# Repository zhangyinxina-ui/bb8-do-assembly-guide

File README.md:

# BB-8 & D-O 1:1 Assembly Guide

[中文在线装配网站](https://zhangyinxina-ui.github.io/bb8-do-assembly-guide/) · [English build guide](https://zhangyinxina-ui.github.io/bb8-do-assembly-guide/en/) · [权利与再分发边界](NOTICE.md)

一个面向个人制作者的公开工程记录：包含《星球大战：原力觉醒》BB-8 的 1:1 屏幕参考 Blender 模型、三视图、内部运动机构、运动学/动力学验证、控制器草案，以及 D-O 合法公开资源和采购门控路线。

## 当前基准

- BB-8 身体球：Ø508 mm。
- 头部最大直径：Ø295 mm。
- 无天线总高：670 mm，对齐 StarWars.com 公开的 0.67 m。
- Blender 主工程 Stage 19 重开审计：386 个总对象、182 个内部对象，其中 150 个制造对象、9 个非制造工程标记和 23 个 `non_fabrication_reference` 预 CAD 门控对象；主文件 SHA-256 为 `ecd9a8b02db7c0b253c06005aaf16e7a8bf10147f8adec9c8900415e18b38af4`。
- 阶段14质量账本：名义8.463 kg、名义质心z=-56.2 mm、最不利角点z=-27.7 mm；0.6 N·m连续扭矩按2×余量时目标加速度降额为0.70 m/s²。17组质量仍需实物称重。
- 双轮差速内车、310 mm 轮距、6+6 磁体随动头和 40 N 装机拉脱力验收合同。
- 编码器轮速 PI + IMU 偏航闭环仿真：直线 RMS 误差 0.00772 m/s、转角 91.20°，传感器过期同周期撤销 PWM。
- ESP32-S3 已编译双正交编码器与 MPU6050 适配；CPR默认为0、静止标定未完成时保持拒动。
- 双 INA226 电流适配、开漏 ALERT、显式限值、过流/堵转回放与11类锁存故障已编译验证；阶段19将原ALERT→EN假设改为适配MDD20A的ALERT_N→PWM许可级，实体测试仍为 `NOT_RUN`。
- 阶段15新增左右电机驱动包络、双散热器、主保险丝、常开接触器、双通道常闭急停、安全继电器、维护断电与系留急停插口；3°动态坡道解析点为0.289 N·m/电机、2.07×连续扭矩裕量和4.22°合成倾角。器件型号与实体测试仍未冻结。
- 阶段16新增19项强制真机调试门、固定字段ESP32遥测解析器和带文件SHA-256的证据审计；当前结果为 `HOLD_PHYSICAL_TESTS_NOT_RUN`，0/19通过。
- 阶段17用厂商官方资料筛选MDD20A、30 A MIDI保险丝、SW60接触器和P28A 4S2P候选；15/15额定检查通过，但因堵转、再生、独立去能适配、BMS与电池包未冻结，结果保持 `HOLD_COMPONENT_FREEZE_MEASUREMENTS_REQUIRED`。
- 阶段18完成REC Active BMS 4S、MDD20A、SW60、MIDI保险丝、外置分流器与双通道门板的模块化电源舱解析布局，并已写入唯一Blender主工程；重开审计确认363个总对象、159个内部对象、150个制造对象、9个工程标记和39个阶段18对象。8个候选包络满足球壳/候选/既有机构间隙门，但12项实物尺寸与接口仍未冻结，结果保持 `HOLD_PHYSICAL_FIT_AND_INTERFACE_VALIDATION_REQUIRED`。
- 阶段19发布双许可PWM门正式KiCad 10原理图与50 × 35 mm两层布线PCB，并把23个非制造板件/器件参考包络写入唯一Blender主工程；重开审计与新导出已通过。SAFE_A、SAFE_B、双INA226 `ALERT_N`与3.3 V掉电均可独立阻断左右PWM；64/64真值组合、0项ERC违规、0项PCB DRC违规、0个未连接项，以及34个器件引用/91条规范引脚连接/21个网络交叉审计通过。但尚无独立原理图/布局同行复核、Gerber/钻孔发布复核、实装板或台架波形，结果保持 `HOLD_PCB_CAD_BENCH_AND_SAFETY_VALIDATION_REQUIRED`。
- 阶段20发现并封锁旧结构分析漂移：当前制造清单的磁力桅杆是Ø24 × 340 mm，而阶段2仍按Ø12/Ø8 × 300 mm铝管计算。新门以当前数字几何筛查2.5 g垂向/1.0 g侧向载荷、斜撑屈曲、纵梁/横梁挠度、PCD35电机安装需求、理想基材疲劳和桅杆模态；解析检查通过，但轮—壳接触还缺5.5 mm径向调节预算，15项材料/连接/公差/实物门全部未关闭，结果保持 `HOLD_JOINT_TOLERANCE_MATERIAL_AND_PHYSICAL_VALIDATION_REQUIRED`。
- D-O v3.4.3 的 D0/D1 舵机—Serial0 冲突已形成固定哈希安全变体：四路舵机移到 D22–D25，Mega 2560 编译仍为 Flash 17% / RAM 18%，并生成版本锁定线束合同；实体导通、USB/Serial0、四路脉宽与失效保护仍为 `NOT_RUN`，不放行舵机电源。
- 24 步装配指南与19项真机门；浏览器进度不能替代真机证据。

这些拆分尺寸和外观细节来自公开画面、社区摄影测量和制作者资料，不是 Lucasfilm 官方 CAD，也不应宣称逐毫米复制电影道具。

## 仓库结构

| 路径 | 内容 |
| --- | --- |
| `blender/` | 参数化生成器、主工程、阶段检查点、审计和导出脚本 |
| `engineering/` | 物理输入、计算结果、D-O 清单和采购门控 |
| `firmware/` | BB-8 C++ 控制核心与 ESP32-S3 适配草案 |
| `docs/` | 从阶段 1 到阶段 20 的中英文设计、验证和续接记录 |
| `hardware/` | 阶段19双许可PWM门正式KiCad原理图、两层布线PCB与OpenSCAD机械包络；不含Gerber/钻孔发布包 |
| `app/` | Vinext/Next 开发网站 |
| `github-pages-src/` | GitHub Pages 纯静态 React 入口 |
| `public/` | 网站公开的图像、GLB、STL、CSV 和说明文件 |
| `tools/` | 运动学、物理、磁耦合、真机证据、D-O 与 Pages 审计工具 |

## 本地运行

要求 Node.js 22.13.0 或更高版本、Python 3，以及可选的 Blender 5.1.x。

```bash
npm ci
npm run dev
```

构建并审计 GitHub Pages 静态网站：

```bash
npm run build:pages
```

完整网站回归测试：

```bash
npm test
npm run lint
```

主要工程验证：

```bash
python3 tools/verify_kinematics.py
python3 tools/verify_physics.py
python3 tools/verify_multibody.py
python3 tools/verify_differential_turn.py
python3 tools/verify_motor_selection.py
python3 tools/verify_magnetic_coupling.py
python3 tools/verify_mass_properties.py
python3 tools/verify_stability_envelope.py
python3 tools/verify_commissioning_evidence.py
python3 tools/verify_power_component_selection.py
python3 tools/verify_power_cassette_layout.py
python3 tools/verify_dual_permissive_gate.py
python3 tools/verify_stage19_kicad.py
python3 tools/verify_stage19_kicad_pcb.py
python3 tools/verify_stage20_structural_load_path.py
python3 tools/audit_do_resources.py
sh tools/run_closed_loop_sim.sh
```

阶段 10 的闭环运动证据见 [编码器 / IMU 闭环运动仿真](docs/BB8_阶段10_闭环运动仿真.md) 和 [200 Hz 遥测](engineering/closed_loop_telemetry.csv)。软件仿真通过不等于真机地面验收。

阶段 11 的传感器代码、默认拒动策略和上电标定顺序见 [ESP32 编码器与 MPU6050 适配](docs/BB8_阶段11_ESP32传感器适配.md) 与 [机器可读接口合同](engineering/sensor_adapter_contract.json)。

阶段 12 的双 INA226、开漏ALERT、显式限值和故障回放见 [电流保护与堵转回放](docs/BB8_阶段12_电流保护与堵转回放.md)、[机器可读电流合同](engineering/power_safety_contract.json) 和 [5 ms回放记录](engineering/power_safety_replay.csv)；当时的EN假设已由阶段19适配为MDD20A的PWM硬件门。

阶段 13 把这条保护链落实到110件内部总成，见 [电流保护硬件建模与重开审计](docs/BB8_阶段13_电流保护硬件建模.md) 和 [110件装配尺寸清单](engineering/internal_assembly_manifest.csv)。

阶段 14 增加可拆卸密封低位配重盒，并以17组质量账本、全部最小/最大角点和刚体惯量替代旧110 mm假设，见 [中文验证报告](docs/BB8_阶段14_质量质心与惯量验证.md)、[English validation report](docs/BB8_stage14_mass_cg_inertia_validation.md) 和 [当前内部装配清单](engineering/internal_assembly_manifest.csv)。

阶段 15 把驱动器与硬件去能链落实为30个新内部对象，并新增斜坡、牵引、转弯、倾角和磁头合载荷扫描，见 [中文阶段15报告](docs/BB8_阶段15_驱动电源与动态稳定性.md)、[English Stage 15 report](docs/BB8_stage15_drive_power_dynamic_stability.md) 和已由阶段19重导出的 [150件制造清单](engineering/internal_assembly_manifest.csv)。未提供机械驻车制动，因此断电坡道保持明确为不支持。

阶段 16 不新增 `.blend` 副本，而是把真实硬件运行转换为19项可审计门：固定字段串口遥测、测量值、证据文件和SHA-256必须同时存在，空填PASS会被拒绝。见 [中文阶段16报告](docs/BB8_阶段16_真机调试证据门.md)、[English Stage 16 report](docs/BB8_stage16_physical_commissioning_evidence_gate.md)、[测试矩阵](engineering/commissioning_test_plan.json)、[证据模板](engineering/commissioning_evidence.json) 和 [当前HOLD结果](engineering/commissioning_results.json)。

阶段 17 将通用电气包络收敛为官方资料支持的候选，但不越过实物证据边界：MDD20A额定裕量足够，却没有独立EN且再生路径未冻结；30 A MIDI必须用堵转波形做I²t配合；SW60普通续流二极管的35 ms典型释放时间超出20 ms合同；4S BMS尚未冻结。见 [中文阶段17报告](docs/BB8_阶段17_驱动电源器件选型门.md)、[English Stage 17 report](docs/BB8_stage17_drive_power_component_selection_gate.md)、[候选矩阵](engineering/power_component_candidates.json) 和 [当前HOLD结果](engineering/power_component_selection_results.json)。

阶段 18 将候选器件收敛为可拆卸模块化驱动电源舱：REC Active BMS 4S按111 × 135 × 44 mm外壳、MDD20A按88.90 × 78.74 mm官方板框、SW60按81 × 37 × 28.1 mm包络进入解析布局。当前最小球壳余量27.643 mm、候选件间隙7.500 mm、与既有机构间隙6.000 mm；这些只证明数字包络未冲突，不代替实物孔位、接插件、线束弯曲、散热与维护验证。几何已覆盖保存到唯一主工程并在重开后通过审计，主文件SHA-256为 `3b774f3e02c89e15922aac48629a43d4765d37078acad88ccf34f6316827d5c3`。见 [中文阶段18报告](docs/BB8_阶段18_模块化驱动电源舱布局门.md)、[English Stage 18 report](docs/BB8_stage18_modular_drive_power_cassette_layout_gate.md)、[布局输入](engineering/stage18_power_cassette_layout.json) 和 [当前HOLD结果](engineering/stage18_power_cassette_results.json)。

阶段 19 将门板占位收敛为正式原理图与布线PCB/DRC参考设计：2个VO617A-4隔离SAFE_A/B，3片SN74LVC2G08依次门控SAFE_A、SAFE_B和双INA226 `ALERT_N`；2.00 kΩ/0.5 W输入支路在12.0–16.8 V解析为5.175–7.900 mA，64行真值表证明任一许可丢失均使两路PWM为低。23个板件/器件包络已作为非制造参考写入唯一主工程，重开后确认386个总对象、182个内部对象、150个制造对象、9个工程标记和23个Stage 19对象；STL/GLB、制造清单与内部三视图已重导出。KiCad 10.0.4正式原理图为0项ERC违规；50 × 35 mm两层PCB含38个封装、1614段走线、54个过孔、F.Cu 3V3和B.Cu GND铜区，DRC为0项违规/0个未连接项。临时重生成板与跟踪板的UUID无关结构哈希一致，XML网表与34个器件引用、91条规范引脚连接和21个网络全部一致。仍没有独立原理图/布局同行复核、Gerber/钻孔发布复核、实装板或20 ms示波器证据。见 [中文阶段19报告](docs/BB8_阶段19_独立双许可PWM硬件门.md)、[English Stage 19 report](docs/BB8_stage19_independent_dual_permissive_pwm_gate.md)、[原理图验证结果](engineering/stage19_kicad_verification.json)、[PCB验证结果](engineering/stage19_kicad_pcb_verification.json)、[PCB DRC报告](engineering/stage19_kicad_pcb_drc.json)、[Blender重开证据](engineering/stage19_blender_reopen_audit.json)、[机器合同](engineering/stage19_dual_permissive_gate_contract.json) 和 [当前HOLD结果](engineering/stage19_dual_permissive_gate_results.json)。

阶段 20 将结构解析重新绑定到当前Stage-19制造清单，并明确标记阶段2的Ø12/Ø8 × 300 mm桅杆已被当前Ø24 × 340 mm包络取代。Ø24/Ø20管材和Ø12/Ø8斜撑只是待冻结候选；2.5 g垂向/1.0 g侧向闭式筛查得到桅杆3.273 MPa、两根纵梁22.814 MPa和0.670 mm挠度，解析裕量通过。PCD35电机面板只报告每颗M4的18.25 N合成需求，不宣称未知等级紧固件已通过。理想6061-T6/T651基材、模态和名义锁扣比值同样只作筛查；轮—壳接触的5.5 mm调节短缺、材料证书、接头、壳体接触、应变、冲击、锤击模态、耐久与19项真机门仍保持开放。见 [中文阶段20报告](docs/BB8_阶段20_结构载荷与公差门.md)、[English Stage 20 report](docs/BB8_stage20_structural_load_and_tolerance_gate.md)、[机器合同](engineering/stage20_structural_load_contract.json)、[当前HOLD结果](engineering/stage20_structural_load_results.json) 和 [载荷扫描](engineering/stage20_structural_load_sweep.csv)。

## D-O 公开资源边界

仓库不冒充拥有 D-O 整机机械文件：

- Printed Droid 公开仓库固定审计到提交 `e90aacdbe26a62fd4f0229d5504a3f2f3c409055`。
- 公开仓库包含 5 个 Arduino 草图，但整机机械 CAD/STL 数量为 0。
- v1.1、v2.1、v3.4 使用个人非商业条款，不能笼统称为 OSI 开源。
- Printed Droid 控制板页的 12 个公开附件已下载到 Git 忽略目录并逐项固定 SHA-256；公开可下载不等于允许本仓库镜像再分发。
- AIO32 v2.1 附件含 22 个源码文件，已用 ESP32 core 3.3.7 实编译通过（Flash 41%、RAM 15%），并发现手册遗漏 SensorLib 依赖；但整包仍无统一 LICENSE、KiCad/Gerber 或机械模型，其手册所称共享仓库硬件文件在当前唯一 `main` 分支中未找到，保持许可与硬件 CAD 双 HOLD。
- Mr Baddeley D-O V2 机械包属于付费资源，本仓库不包含。
- Mantis 播放列表的5集编号构建视频与1个轮胎视频描述已逐条审计；描述没有发布 Matt 改版 CAD 或控制源码，详见 [机器审计](engineering/do_mantis_video_audit.json)。
- 许可不明确的调试支架、第三方 PDF、本地工具链和编译缓存不会推送到 GitHub。

详见 [D-O 资源审计与自组入口](docs/DO_资源审计与自组入口.md)、[D01-D16 自组路线](docs/DO_自组采购与调试路线.md) 和 [26 项采购门控 BOM](engineering/do_self_build_bom.csv)。`DO-SRC-001` 已有 D22–D25 可编译变体但仍等待实体连续性；`DO-SRC-002` 已有版本/哈希绑定线束合同但仍等待逐网导通；`DO-SRC-003` 将官网仍为 v3.4.0 的泛名 ZIP 降为历史参考，当前转换输入只使用固定 GitHub v3.4.3。

## 自动部署

推送到 `main` 后，`.github/workflows/deploy-pages.yml` 会：

1. 安装固定依赖；
2. 构建 `/bb8-do-assembly-guide/` 子路径静态站点；
3. 扫描本机绝对路径、GitHub 令牌和禁止发布的 `.blend` 网站副本；
4. 上传 Pages artifact 并部署到 GitHub Pages。

## 免责声明

这是非官方粉丝研究、个人教育和工程原型。STAR WARS、BB-8、D-O 及相关角色归各自权利人所有。除非文件单独声明许可证，本仓库公开可见不等于自动授予商用、复制或再分发许可。使用前请阅读 [NOTICE.md](NOTICE.md)。

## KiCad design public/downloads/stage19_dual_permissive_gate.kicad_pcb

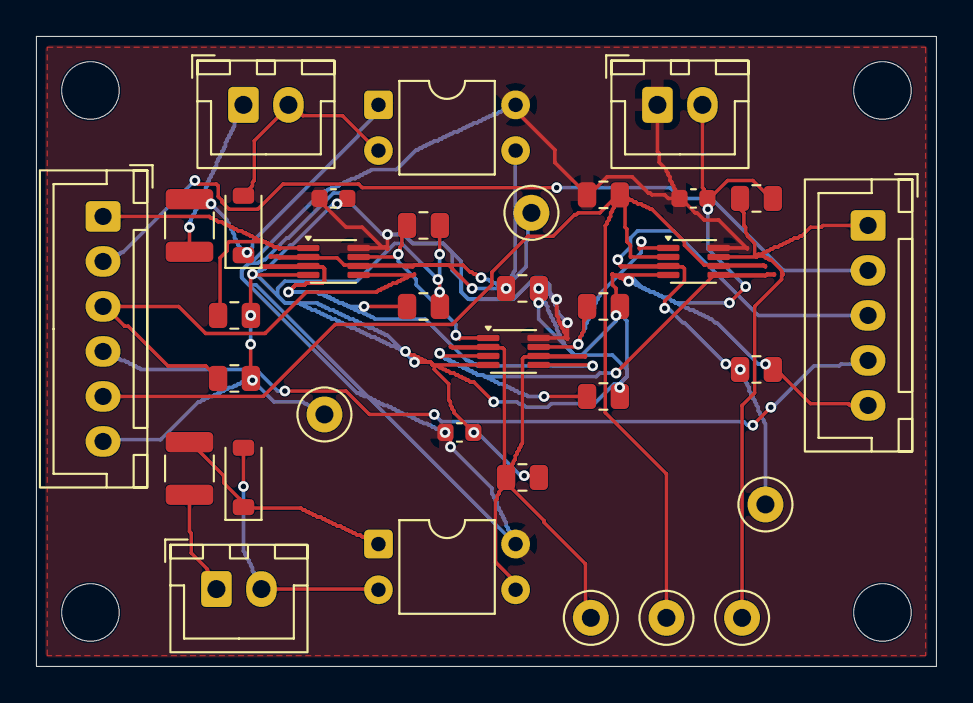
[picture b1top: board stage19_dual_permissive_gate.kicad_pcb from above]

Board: 2 copper layers, 50.0 x 35.0 mm, 38 parts (0 on the bottom side), 21 nets.

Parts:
C1, C2, C3: 100nF; C_0603_1608Metric
D1, D2: 1N4148W; D_SOD-123
H1, H2, H3, H4: M3 INSULATED; MountingHole_3.2mm_M3
J1: LOGIC POWER 3V3; JST_XH_B2B-XH-A_1x02_P2.50mm_Vertical
J2: MCU PWM DIR ALERT; JST_XH_B6B-XH-A_1x06_P2.50mm_Vertical
J3: MDD20A PWM DIR; JST_XH_B5B-XH-A_1x05_P2.50mm_Vertical
J4: SAFE A 12-16V8; JST_XH_B2B-XH-A_1x02_P2.50mm_Vertical
J5: SAFE B 12-16V8; JST_XH_B2B-XH-A_1x02_P2.50mm_Vertical
R1, R2: 2.00k 1% 0.5W; R_1210_3225Metric
R3, R4: 4.70k 1%; R_0805_2012Metric
R5, R6, R7, R8, R9, R10, R11, R12, R13: 10.0k 1%; R_0805_2012Metric
TP1: SAFE_A_OK; TestPoint_Loop_D2.50mm_Drill1.0mm
TP2: SAFE_B_OK; TestPoint_Loop_D2.50mm_Drill1.0mm
TP3: ALERT_N; TestPoint_Loop_D2.50mm_Drill1.0mm
TP4: PWM_L_OUT; TestPoint_Loop_D2.50mm_Drill1.0mm
TP5: PWM_R_OUT; TestPoint_Loop_D2.50mm_Drill1.0mm
TP6: GND; TestPoint_Loop_D2.50mm_Drill1.0mm
U1, U2: VO617A-4; DIP-4_W7.62mm
U3, U4, U5: SN74LVC2G08DCU; VSSOP-8_2.3x2mm_P0.5mm

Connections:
3V3: C1.1, C2.1, C3.1, J1.1, R13.1, U1.4, U2.4, U3.8, U4.8, U5.8
ALERT_N: J2.5, R13.2, TP3.1, U5.2, U5.6
DIR_L: J2.2, J3.2
DIR_R: J2.4, J3.4
GND: C1.2, C2.2, C3.2, J1.2, J2.6, J3.5, R3.2, R4.2, R5.2, R6.2, R7.2, R8.2, R9.2, R10.2, R11.2, R12.2, TP6.1, U3.4, U4.4, U5.4
PWM_L_A: R7.1, U3.7, U4.1
PWM_L_AB: R9.1, U4.7, U5.1
PWM_L_IN: J2.1, R5.1, U3.1
PWM_L_OUT: J3.1, R11.1, TP4.1, U5.7
PWM_R_A: R8.1, U3.3, U4.5
PWM_R_AB: R10.1, U4.3, U5.5
PWM_R_IN: J2.3, R6.1, U3.5
PWM_R_OUT: J3.3, R12.1, TP5.1, U5.3
SAFE_A_LED_A: D1.1, R1.2, U1.1
SAFE_A_OK: R3.1, TP1.1, U1.3, U3.2, U3.6
SAFE_A_PLUS: J4.1, R1.1
SAFE_A_RETURN: D1.2, J4.2, U1.2
SAFE_B_LED_A: D2.1, R2.2, U2.1
SAFE_B_OK: R4.1, TP2.1, U2.3, U4.2, U4.6
SAFE_B_PLUS: J5.1, R2.1
SAFE_B_RETURN: D2.2, J5.2, U2.2

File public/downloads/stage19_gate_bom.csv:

reference,quantity,category,manufacturer,part_number,value_or_package,release_status,official_source,note
PCB1,1,pcb,TBD,CUSTOM_STAGE19_GATE,50x35x1.6 mm 2-layer FR-4,NOT_RELEASED_NO_KICAD_OR_GERBER,,Four 3.2 mm mounting holes; fabrication prohibited until ERC/DRC/review
U1 U2,2,optocoupler,Vishay,VO617A-4,DIP-4,REFERENCE_SELECTED,https://www.vishay.com/docs/83430/vo617a.pdf,CTR bin 160-320% only specified at IF=5 mA VCE=5 V and 25 C
U3 U4 U5,3,logic,Texas Instruments,SN74LVC2G08DCU,VSSOP-8,REFERENCE_SELECTED,https://www.ti.com/lit/ds/symlink/sn74lvc2g08.pdf,One dual gate package per permissive stage
R1 R2,2,resistor,TBD,TBD,2.00 kOhm 1% 0.5 W,VALUE_FROZEN_PART_TBD,,Safety-loop LED current limit
R3 R4,2,resistor,TBD,TBD,4.70 kOhm 1% >=0.1 W,VALUE_FROZEN_PART_TBD,,SAFE_A_OK and SAFE_B_OK emitter pull-down
R5 R6,2,resistor,TBD,TBD,10.0 kOhm 1% >=0.1 W,VALUE_FROZEN_PART_TBD,,MCU PWM input pull-down
R7 R8,2,resistor,TBD,TBD,10.0 kOhm 1% >=0.1 W,VALUE_FROZEN_PART_TBD,,U3 intermediate pull-down
R9 R10,2,resistor,TBD,TBD,10.0 kOhm 1% >=0.1 W,VALUE_FROZEN_PART_TBD,,U4 intermediate pull-down
R11 R12,2,resistor,TBD,TBD,10.0 kOhm 1% >=0.1 W,VALUE_FROZEN_PART_TBD,,Final MDD20A PWM output fail-low pull-down
R13,1,resistor,TBD,TBD,10.0 kOhm 1% >=0.1 W,VALUE_FROZEN_PART_TBD,,ALERT_N pull-up; open ALERT wiring is not fail-safe
C1 C2 C3,3,capacitor,TBD,TBD,100 nF X7R >=10 V,VALUE_FROZEN_PART_TBD,,One local decoupler per LVC package
D1 D2,2,diode,TBD,1N4148W,SOD-123,REFERENCE_SELECTED_PART_VENDOR_TBD,,Anti-parallel reverse clamp for each optocoupler LED
J1 J4 J5,3,connector,JST,B2B-XH-A,2-position 2.5 mm top-entry,REFERENCE_SELECTED,https://www.jst-mfg.com/product/pdf/eng/eXH.pdf,Logic power and independent safety inputs
J2,1,connector,JST,B6B-XH-A,6-position 2.5 mm top-entry,REFERENCE_SELECTED,https://www.jst-mfg.com/product/pdf/eng/eXH.pdf,MCU PWM DIR ALERT_N and GND
J3,1,connector,JST,B5B-XH-A,5-position 2.5 mm top-entry,REFERENCE_SELECTED,https://www.jst-mfg.com/product/pdf/eng/eXH.pdf,MDD20A PWM DIR and GND
TP1 TP2 TP3 TP4 TP5 TP6,6,test_point,TBD,TBD,1.0 mm loop or pad,FOOTPRINT_TBD,,SAFE_A_OK SAFE_B_OK ALERT_N PWM_L_OUT PWM_R_OUT and GND
H1 H2 H3 H4,4,mounting,TBD,TBD,M3 insulated standoff hardware,MECHANICAL_CANDIDATE,,Keep conductive hardware clear of logic and isolated input copper
